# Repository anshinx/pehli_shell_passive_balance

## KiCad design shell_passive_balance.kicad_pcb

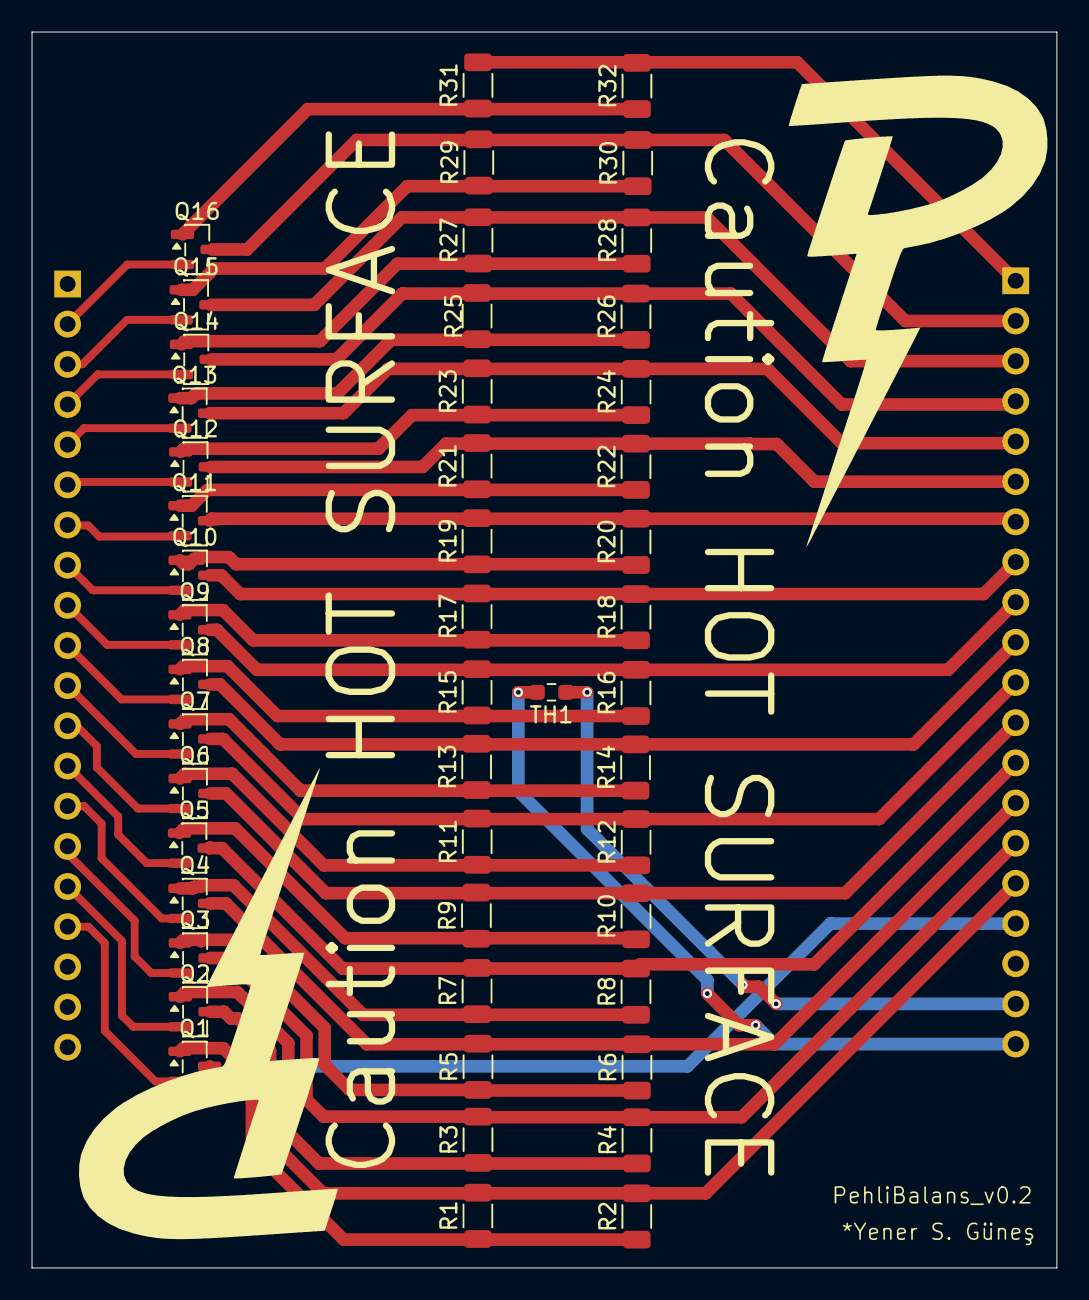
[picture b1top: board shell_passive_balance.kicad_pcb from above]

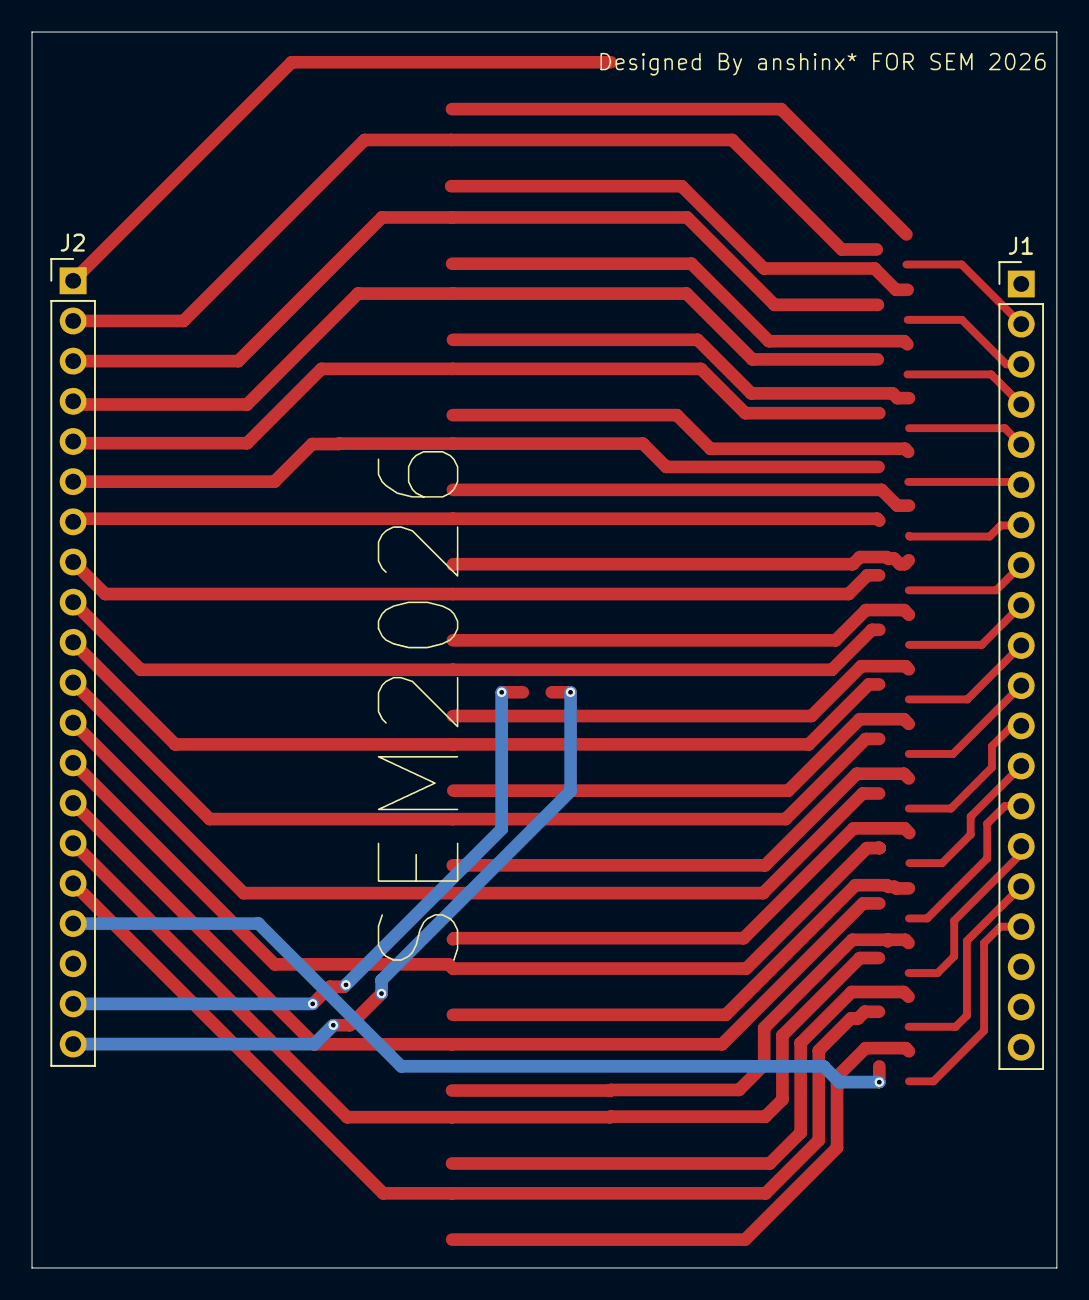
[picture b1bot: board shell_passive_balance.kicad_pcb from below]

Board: 4 copper layers, 64.8 x 78.2 mm, 51 parts (2 on the bottom side), 51 nets.

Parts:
J1, J2: Conn_01x20_Pin; PinHeader_1x20_P2.54mm_Vertical
Q1, Q2, Q3, Q4, Q5, Q6, Q7, Q8, Q9, Q10, Q11, Q12, Q13, Q14, Q15, Q16: PMOS; SOT-23
R1, R2, R3, R4, R5, R6, R7, R8, R9, R10, R11, R12, R13, R14, R15, R16, R17, R18, R19, R20, R21, R22, R23, R24, R25, R26, R27, R28, R29, R30, R31, R32: 33R; R_1206_3216Metric
TH1: Thermistor_NTC; R_0603_1608Metric_Pad0.98x0.95mm_HandSolder

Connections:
/B_0: J2.1, R31.2, R32.2
/B_1: J2.2, Q16.3 (S), R29.2, R30.2
/B_2: J2.3, Q15.3 (S), R27.2, R28.2
/B_3: J2.4, Q14.3 (S), R25.2, R26.2
/B_4: J2.5, Q13.3 (S), R23.2, R24.2
/B_5: J2.6, Q12.3 (S), R21.2, R22.2
/B_6: J2.7, Q11.3 (S), R19.2, R20.2
/B_7: J2.8, Q10.3 (S), R17.2, R18.2
/B_8: J2.9, Q9.3 (S), R15.2, R16.2
/B_9: J2.10, Q8.3 (S), R13.2, R14.2
/B_10: J2.11, Q7.3 (S), R11.2, R12.2
/B_11: J2.12, Q6.3 (S), R9.2, R10.2
/B_12: J2.13, Q5.3 (S), R7.2, R8.2
/B_13: J2.14, Q4.3 (S), R5.2, R6.2
/B_14: J2.15, Q3.3 (S), R3.2, R4.2
/B_15: J2.16, Q2.3 (S), R1.2, R2.2
/B_16: J2.17, Q1.3 (S)
/CI_1: J1.2, Q16.2 (G)
/CI_2: J1.3, Q15.2 (G)
/CI_3: J1.4, Q14.2 (G)
/CI_4: J1.5, Q13.2 (G)
/CI_5: J1.6, Q12.2 (G)
/CI_6: J1.7, Q11.2 (G)
/CI_7: J1.8, Q10.2 (G)
/CI_8: J1.9, Q9.2 (G)
/CI_9: J1.10, Q8.2 (G)
/CI_10: J1.11, Q7.2 (G)
/CI_11: J1.12, Q6.2 (G)
/CI_12: J1.13, Q5.2 (G)
/CI_13: J1.14, Q4.2 (G)
/CI_14: J1.15, Q3.2 (G)
/CI_15: J1.16, Q2.2 (G)
/CI_16: J1.17, Q1.2 (G)
/NTC+: J2.19, TH1.1
/NTC-: J2.20, TH1.2
unnamed: Q1.1 (D), R1.1, R2.1
unnamed: Q2.1 (D), R3.1, R4.1
unnamed: Q3.1 (D), R5.1, R6.1
unnamed: Q4.1 (D), R7.1, R8.1
unnamed: Q5.1 (D), R9.1, R10.1
unnamed: Q6.1 (D), R11.1, R12.1
unnamed: Q7.1 (D), R13.1, R14.1
unnamed: Q8.1 (D), R15.1, R16.1
unnamed: Q9.1 (D), R17.1, R18.1
unnamed: Q10.1 (D), R19.1, R20.1
unnamed: Q11.1 (D), R21.1, R22.1
unnamed: Q12.1 (D), R23.1, R24.1
unnamed: Q13.1 (D), R25.1, R26.1
unnamed: Q14.1 (D), R27.1, R28.1
unnamed: Q15.1 (D), R29.1, R30.1
unnamed: Q16.1 (D), R31.1, R32.1

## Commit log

2026-02-11 customised gui
2026-02-11 finalised product
